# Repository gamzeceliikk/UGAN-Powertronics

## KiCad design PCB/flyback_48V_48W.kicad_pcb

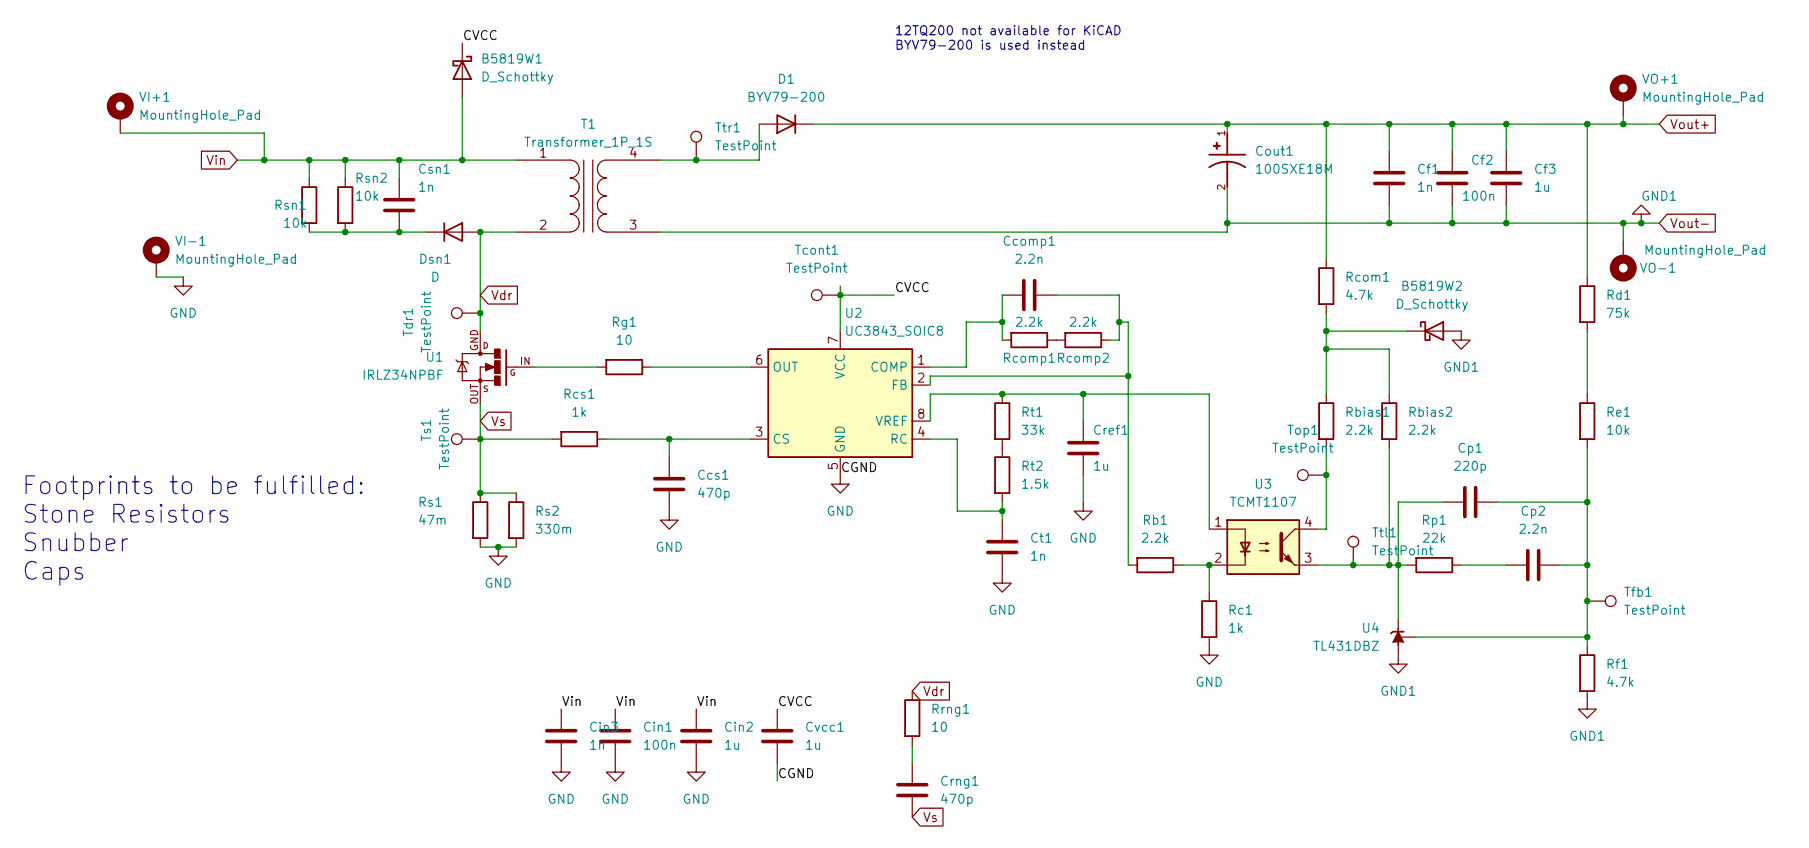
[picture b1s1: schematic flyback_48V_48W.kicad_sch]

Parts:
B5819W1, B5819W2: D_Schottky; D_SOD-123
Ccomp1: 2.2n; C_1206_3216Metric_Pad1.33x1.80mm_HandSolder
Ccs1: 470p; C_1206_3216Metric_Pad1.33x1.80mm_HandSolder
Cf1: 1n; C_1206_3216Metric_Pad1.33x1.80mm_HandSolder
Cf2: 100n; C_1206_3216Metric_Pad1.33x1.80mm_HandSolder
Cf3: 1u; C_1206_3216Metric_Pad1.33x1.80mm_HandSolder
Cin1: 100n; C_1206_3216Metric_Pad1.33x1.80mm_HandSolder
Cin2: 1u; C_1206_3216Metric_Pad1.33x1.80mm_HandSolder
Cin3: 1n; C_1206_3216Metric_Pad1.33x1.80mm_HandSolder
Cout1: 100SXE18M; CAPPRD500W60D1000H1300; PARTREV 5-Mar-21
Cp1: 220p; C_1206_3216Metric_Pad1.33x1.80mm_HandSolder
Cp2: 2.2n; C_1206_3216Metric_Pad1.33x1.80mm_HandSolder
Cref1: 1u; C_1206_3216Metric_Pad1.33x1.80mm_HandSolder
Crng1: 470p; C_1206_3216Metric_Pad1.33x1.80mm_HandSolder
Csn1: 1n; C_1206_3216Metric_Pad1.33x1.80mm_HandSolder
Ct1: 1n; C_1206_3216Metric_Pad1.33x1.80mm_HandSolder
Cvcc1: 1u; C_1206_3216Metric_Pad1.33x1.80mm_HandSolder
D1: BYV79-200; TO-220-2_Vertical
Dsn1: D; D_SOD-123
Rb1: 2.2k; R_1206_3216Metric_Pad1.30x1.75mm_HandSolder
Rbias1, Rbias2: 2.2k; R_1206_3216Metric_Pad1.30x1.75mm_HandSolder
Rc1: 1k; R_1206_3216Metric_Pad1.30x1.75mm_HandSolder
Rcom1: 4.7k; R_1206_3216Metric_Pad1.30x1.75mm_HandSolder
Rcomp1, Rcomp2: 2.2k; R_1206_3216Metric_Pad1.30x1.75mm_HandSolder
Rcs1: 1k; R_1206_3216Metric_Pad1.30x1.75mm_HandSolder
Rd1: 75k; R_1206_3216Metric_Pad1.30x1.75mm_HandSolder
Re1: 10k; R_1206_3216Metric_Pad1.30x1.75mm_HandSolder
Rf1: 4.7k; R_1206_3216Metric_Pad1.30x1.75mm_HandSolder
Rg1: 10; R_1206_3216Metric_Pad1.30x1.75mm_HandSolder
Rp1: 22k; R_1206_3216Metric_Pad1.30x1.75mm_HandSolder
Rrng1: 10; R_1206_3216Metric_Pad1.30x1.75mm_HandSolder
Rs1: 47m; R_2512_6332Metric_Pad1.40x3.35mm_HandSolder
Rs2: 330m; R_2512_6332Metric_Pad1.40x3.35mm_HandSolder
Rsn1, Rsn2: 10k; R_1206_3216Metric_Pad1.30x1.75mm_HandSolder
Rt1: 33k; R_1206_3216Metric_Pad1.30x1.75mm_HandSolder
Rt2: 1.5k; R_1206_3216Metric_Pad1.30x1.75mm_HandSolder
T1: Transformer_1P_1S; RM12_B65816
Tcont1: TestPoint; TestPoint_THTPad_D1.0mm_Drill0.5mm
Tdr1: TestPoint; TestPoint_THTPad_D1.0mm_Drill0.5mm
Tfb1: TestPoint; TestPoint_THTPad_D1.0mm_Drill0.5mm
Top1: TestPoint; TestPoint_THTPad_D1.0mm_Drill0.5mm
Ts1: TestPoint; TestPoint_THTPad_D1.0mm_Drill0.5mm
Ttl1: TestPoint; TestPoint_THTPad_D1.0mm_Drill0.5mm
Ttr1: TestPoint; TestPoint_THTPad_D1.0mm_Drill0.5mm
U1: IRLZ34NPBF; TO-220_with_heatsink
U2: UC3843_SOIC8; SOIC-8_3.9x4.9mm_P1.27mm
U3: TCMT1107; SOP-4_4.4x2.6mm_P1.27mm
U4: TL431DBZ; SOT-23
VI+1: MountingHole_Pad; MountingHole_4.3mm_M4_DIN965_Pad_TopBottom
VI-1: MountingHole_Pad; MountingHole_4.3mm_M4_DIN965_Pad_TopBottom
VO+1: MountingHole_Pad; MountingHole_4.3mm_M4_DIN965_Pad_TopBottom
VO-1: MountingHole_Pad; MountingHole_4.3mm_M4_DIN965_Pad_TopBottom

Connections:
/CVCC: B5819W1.1 (K), Cvcc1.1, Tcont1.1, U2.7 (VCC)
GND: Ccs1.2, Cin1.2, Cin2.2, Cin3.2, Cref1.2, Ct1.2, Cvcc1.2, Rc1.2, Rs1.2, Rs2.2, U2.5 (GND), VI-1.1
unnamed: B5819W2.1 (K), Rbias1.1, Rbias2.1, Rcom1.2
unnamed: Ccomp1.1, Rb1.2, Rcomp2.1, U2.2 (FB)
unnamed: Ccomp1.2, Rcomp1.2, U2.1 (COMP)
unnamed: Ccs1.1, Rcs1.1, U2.3 (CS)
unnamed: Cp1.1, Cp2.1, Re1.2, Rf1.1, Tfb1.1, U4.2 (REF)
unnamed: Cp1.2, Rbias2.2, Rp1.2, Ttl1.1, U3.3, U4.1 (K)
unnamed: Cp2.2, Rp1.1
unnamed: Cref1.1, Rt1.1, U2.8 (VREF), U3.1
unnamed: Crng1.1, Rrng1.2
unnamed: Csn1.2, Dsn1.1 (K), Rsn1.2, Rsn2.2
unnamed: Ct1.1, Rt2.2, U2.4 (RC)
unnamed: D1.2 (A), T1.4 (SB), Ttr1.1
unnamed: Rb1.1, Rc1.1, U3.2
unnamed: Rbias1.2, Top1.1, U3.4
unnamed: Rcomp1.1, Rcomp2.2
unnamed: Rd1.2, Re1.1
unnamed: Rg1.1, U2.6 (OUT)
unnamed: Rg1.2, U1.IN
unnamed: Rt1.2, Rt2.1
Vdr: Dsn1.2 (A), Rrng1.1, T1.2 (AB), Tdr1.1, U1.GND
Vin: B5819W1.2 (A), Cin1.1, Cin2.1, Cin3.1, Csn1.1, Rsn1.1, Rsn2.1, T1.1 (AA), VI+1.1
Vout+: Cf1.1, Cf2.1, Cf3.1, Cout1.1, D1.1 (K), Rcom1.1, Rd1.1, VO+1.1
Vout-: B5819W2.2 (A), Cf1.2, Cf2.2, Cf3.2, Cout1.2, Rf1.2, T1.3 (SA), U4.3 (A), VO-1.1
Vs: Crng1.2, Rcs1.2, Rs1.1, Rs2.1, Ts1.1, U1.OUT

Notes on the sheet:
12TQ200 not available for KiCAD BYV79-200 is used instead
Footprints to be fulfilled: Stone Resistors Snubber Caps

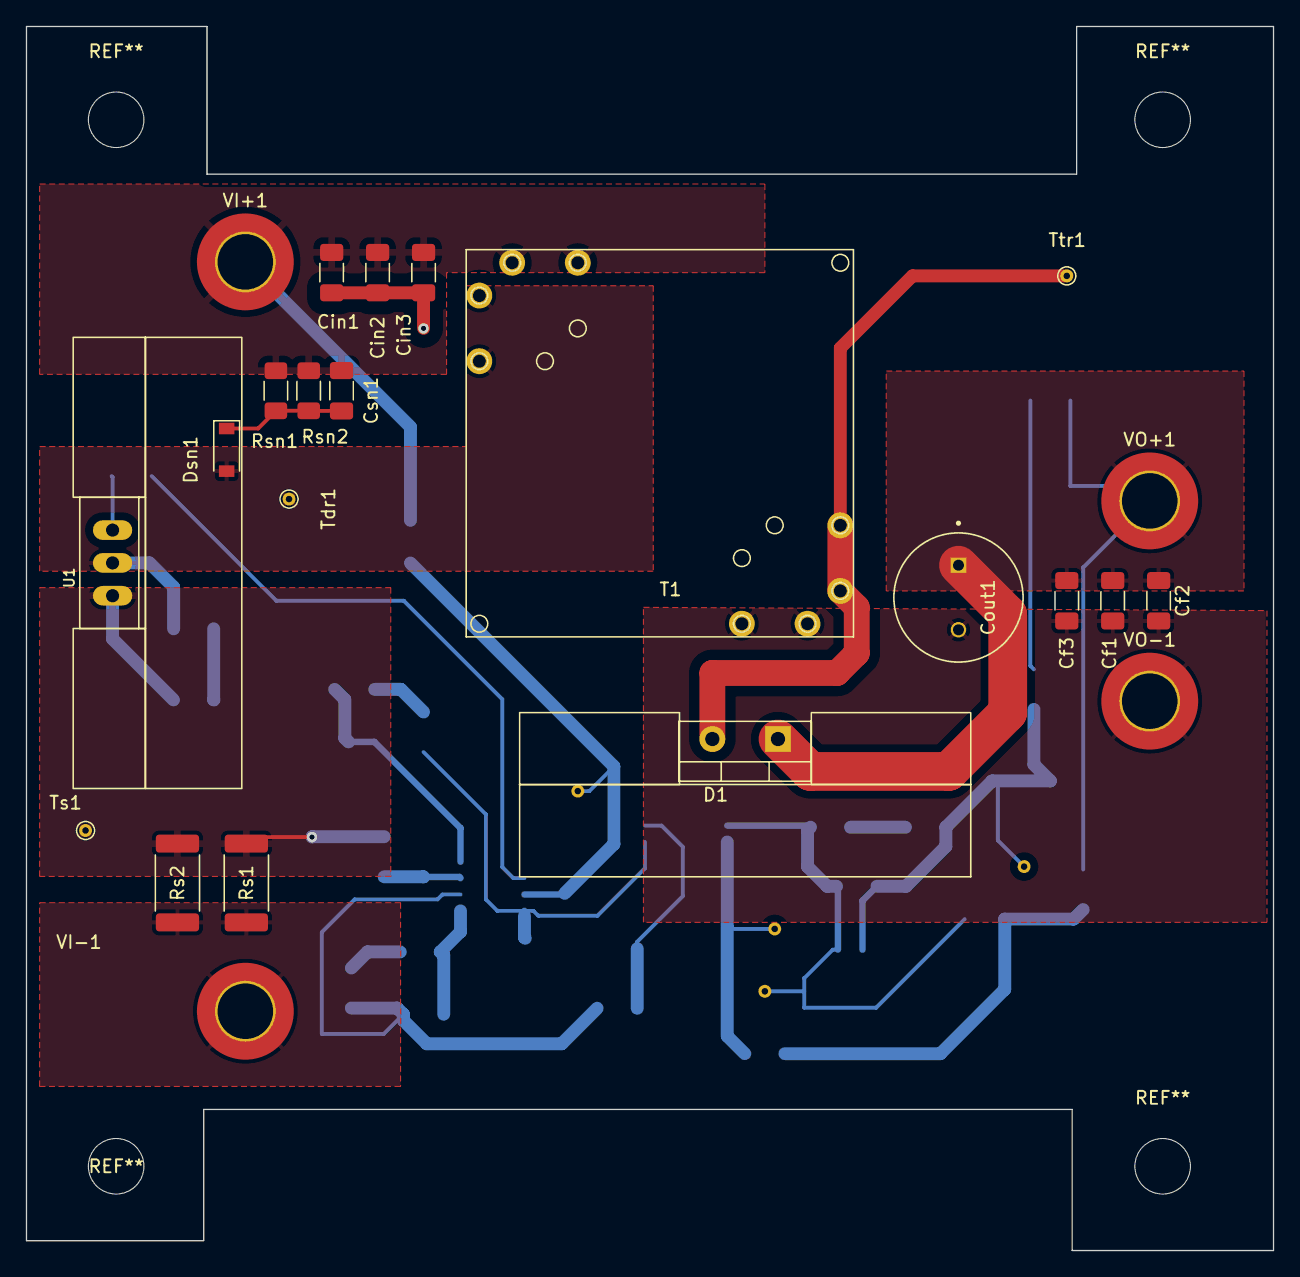
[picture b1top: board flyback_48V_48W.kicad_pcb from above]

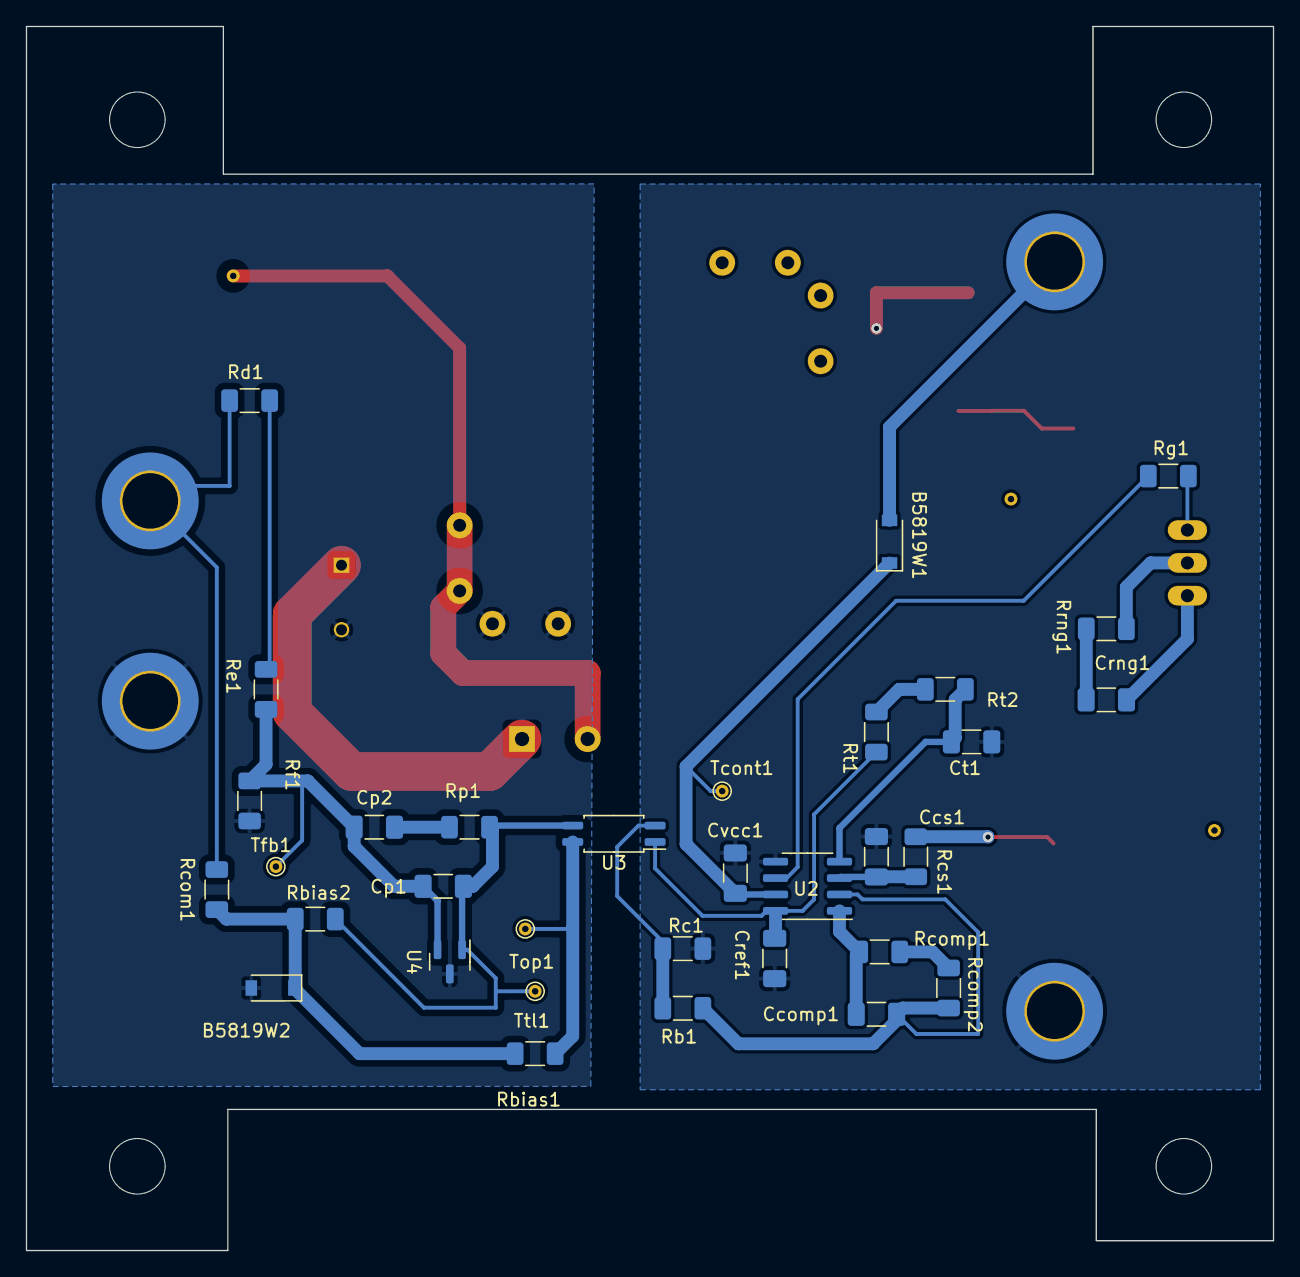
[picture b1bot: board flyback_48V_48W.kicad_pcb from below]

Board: 2 copper layers, 96.5 x 94.7 mm, 56 parts (33 on the bottom side), 26 nets.

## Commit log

2023-04-30 Simulation Report
2023-05-04 Flyback Simulation with Measurements
2023-05-04 Create Simulation Plots
2023-05-04 Simulation Plots
2023-05-05 comprehensive simulation file
    All potential losses (core losses, winding losses, leakage inductance, diode and MOSFET on resistance, capacitor ESR) are included.
2023-05-05 small changes on the simulation file
2023-05-05 Simulation Report & HW2
2023-05-06 Create Controller Notes
2023-05-07 Controller Parameters, Controllers Investigated, etc.
2023-05-21 Error Amp Simulation
2023-06-13 Schematic PCB Gerber and Drill Files
2023-06-13 Gerber Files
2023-06-13 Drill Files
2023-06-13 Kicad schematic, pcb, gerber, drill files
2023-06-13 Create ss
2023-06-13 Create dsa
2023-06-14 description of the directory
2023-06-15 Required files for Manufacruring
2023-06-15 Reuqired Manufacturing Files
2023-06-15 Update description
2023-06-15 Required Files for MANUFACTURİNG
2023-06-27 Full circuit simulaiton
